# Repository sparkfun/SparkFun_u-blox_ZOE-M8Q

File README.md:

SparkFun u-blox ZOE-M8Q
========================================

[*SparkFun u-blox ZOE-M8Q (GPS-15193)*](https://www.sparkfun.com/products/15193)

The ZOE-M8Q is a high quality GPS with equally impressive configurability.  We broke out the basic pins and added all the supporting circuitry to make this module even easier to use.  

Repository Contents
-------------------

* **/Documentation** - Data sheets, additional product information
* **/Hardware** - Eagle design files (.brd, .sch)
* **/Production** - Production panel files (.brd)

Documentation
--------------
* **[Installing an Arduino Library Guide](https://learn.sparkfun.com/tutorials/installing-an-arduino-library)** - Basic information on how to install an Arduino library.
* **[Library](https://github.com/sparkfun/SparkFun_u-blox_GNSS_Arduino_Library)** - Arduino Library used with the SparkFun ZOE-M8Q 
* **[Hookup Guide](https://learn.sparkfun.com/tutorials/sparkfun-gps-breakout-zoe-m8q-and-sam-m8q-hookup-guide)** - Basic hookup guide for the SparkFun ZOE-M8Q.

License Information
-------------------

This product is _**open source**_! 

Please review the LICENSE.md file for license information. 

If you have any questions or concerns on licensing, please contact technical support on our [SparkFun forums](https://forum.sparkfun.com/viewforum.php?f=152).

Distributed as-is; no warranty is given.

- Your friends at SparkFun.

_<COLLABORATION CREDIT>_

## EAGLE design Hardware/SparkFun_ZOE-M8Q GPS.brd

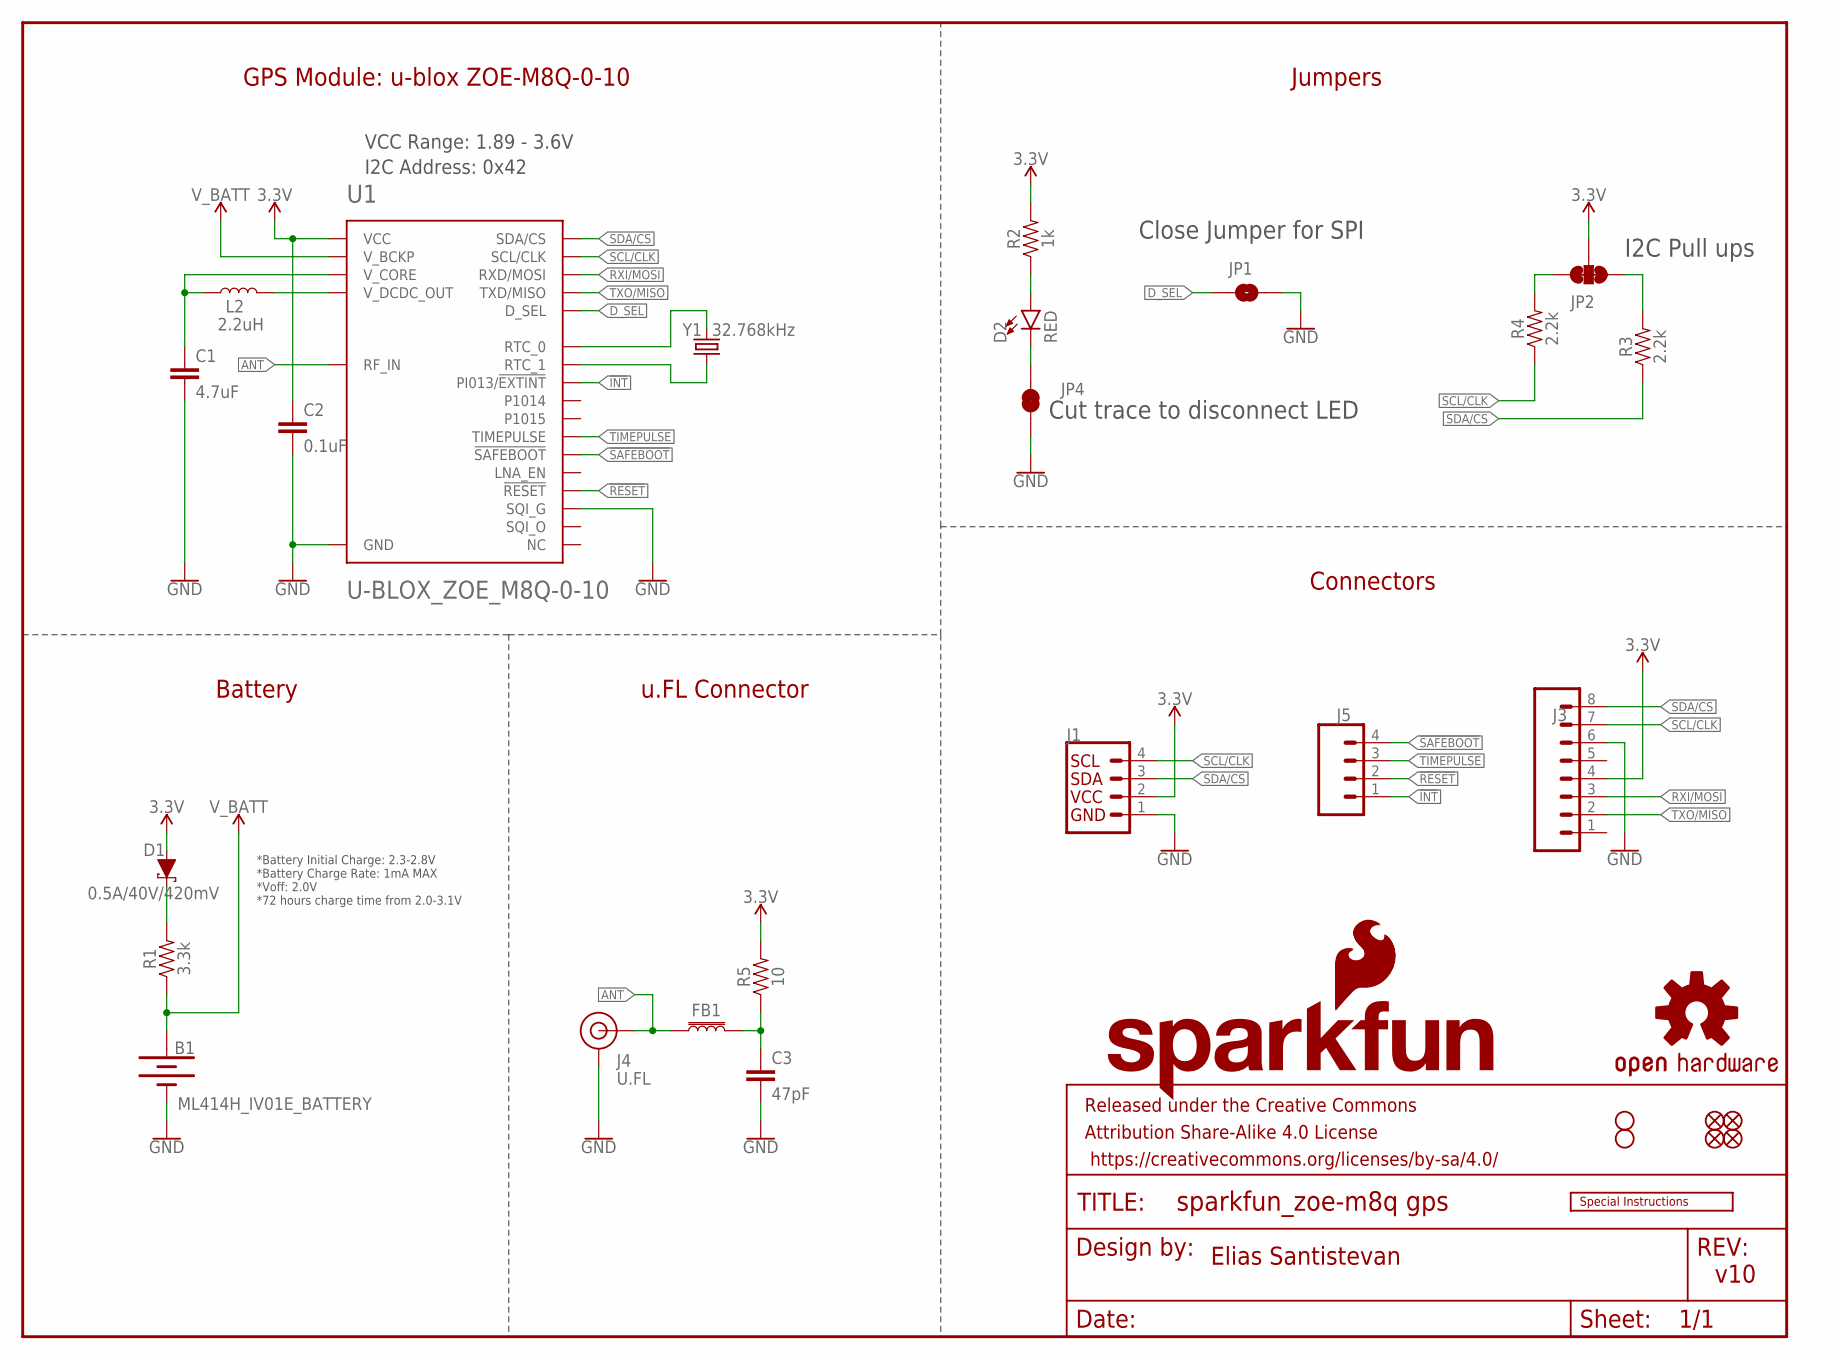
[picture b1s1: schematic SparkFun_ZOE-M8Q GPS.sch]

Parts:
B1: ML414H_IV01E_BATTERY; ML414H_IV01E
C1: 4.7uF; 0603
C2: 0.1uF; 0603
C3: 47pF; 0603
D1: 0.5A/40V/420mV; SOD-323
D2: RED; LED-0603
FB1: FERRITE_BEAD-120_OHM-0402; 0402
FD1, FD2, FD3, FD4: FIDUCIALUFIDUCIAL; FIDUCIAL-MICRO
FRAME1: FRAME-LETTER; CREATIVE_COMMONS
H2, H3: STAND-OFFTIGHT; STAND-OFF-TIGHT
J1: QWIIC_CONNECTORJS-1MM; JST04_1MM_RA
J3: CONN_08NO_SILK_FEMALE_PTH; 1X08_NO_SILK
J4: U.FL
J5: CONN_041X04_NO_SILK; 1X04_NO_SILK
JP1: JUMPER-SMT_2_NO_SILK; SMT-JUMPER_2_NO_SILK
JP2: JUMPER-SMT_3_2-NC_TRACE_SILK; SMT-JUMPER_3_2-NC_TRACE_SILK
JP4: JUMPER-SMT_2_NC_TRACE_SILK; SMT-JUMPER_2_NC_TRACE_SILK
L2: 2.2uH; 0806
LOGO1: SFE_LOGO_NAME_FLAME.1_INCH; SFE_LOGO_NAME_FLAME_.1
LOGO2: OSHW-LOGOS; OSHW-LOGO-S
LOGO3: SFE_LOGO_FLAME.1_INCH; SFE_LOGO_FLAME_.1
LOGO4: SPECIAL_INSTRUCTIONS-ORDERING; ORDERING_INSTRUCTIONS
R1: 3.3k; 0603
R2: 1k; 0603
R3, R4: 2.2k; 0603
R5: 10; 0603
U1: U-BLOX_ZOE_M8Q-0-10; UBLOX_ZOE_M8-0-10
Y1: 32.768kHz; CRYSTAL-SMD-3.2X1.5MM

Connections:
3.3V: C2.1, D1.A, J1.2, J3.4, JP2.2, R2.2, R5.2, U1.24 (VCC), U1.25 (VCC)
!INT: J5.1, U1.43 (PI013/!EXTINT)
!RESET: J5.2, U1.20 (!RESET)
!SAFEBOOT: J5.4, U1.34 (!SAFEBOOT)
ANT: FB1.1, J4.FEED (SIGNAL), U1.4 (RF_IN)
D_SEL: JP1.1, U1.48 (D_SEL)
GND: B1.-, C1.2, C2.2, C3.2, J1.1, J3.6, J4.1 (GND), J4.2 (GND), JP1.2, JP4.1, U1.1 (GND), U1.3 (GND), U1.5 (GND), U1.7 (GND), U1.8 (GND), U1.9 (GND), U1.10 (GND), U1.11 (GND), U1.12 (GND), U1.17 (GND), U1.23 (GND), U1.29 (SQI_G), U1.31 (SQI_G), U1.37 (GND), U1.38 (GND), U1.39 (GND), U1.40 (GND), U1.41 (GND), U1.44 (GND), U1.46 (SQI_G), U1.47 (SQI_G), U1.49 (GND)
unnamed: JP2.1, R3.2
unnamed: D1.C, R1.2
unnamed: JP2.3, R4.2
unnamed: D2.A, R2.1
unnamed: C1.1, L2.1, U1.27 (V_CORE)
unnamed: L2.2, U1.26 (V_DCDC_OUT)
unnamed: D2.C, JP4.2
unnamed: C3.1, FB1.2, R5.1
unnamed: U1.18 (RTC_0), Y1.P$2 (2)
unnamed: U1.19 (RTC_1), Y1.P$1 (1)
RXI/MOSI: J3.3, U1.22 (RXD/MOSI)
SCL/CLK: J1.4, J3.7, R4.1, U1.32 (SCL/CLK)
SDA/CS: J1.3, J3.8, R3.1, U1.2 (SDA/CS)
TIMEPULSE: J5.3, U1.33 (TIMEPULSE)
TXO/MISO: J3.2, U1.21 (TXD/MISO)
V_BATT: B1.+, R1.1, U1.16 (V_BCKP)

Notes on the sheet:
v10
Elias Santistevan
GPS Module: u-blox ZOE-M8Q-0-10
Battery
Connectors
Jumpers
Close Jumper for SPI
I2C Pull ups
Cut trace to disconnect LED
u.FL Connector
*Battery Initial Charge: 2.3-2.8V *Battery Charge Rate: 1mA MAX *Voff: 2.0V *72 hours charge time from 2.0-3.1V
VCC Range: 1.89 - 3.6V
I2C Address: 0x42

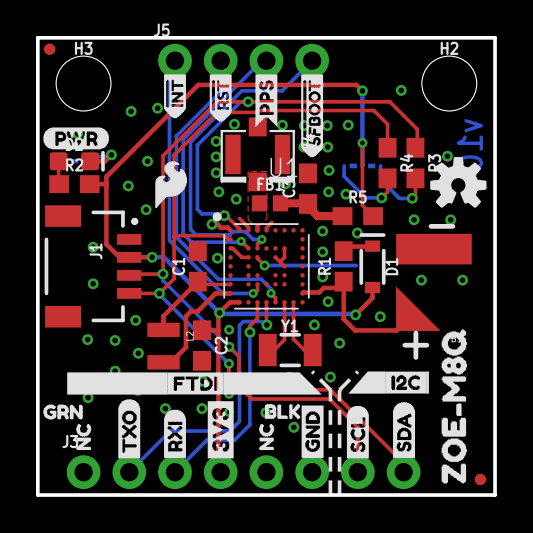
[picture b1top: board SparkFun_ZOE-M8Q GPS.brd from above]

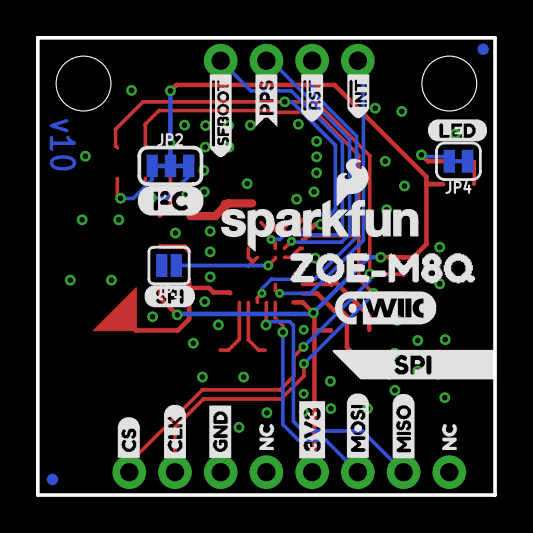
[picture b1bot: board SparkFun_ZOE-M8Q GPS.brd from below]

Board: 2 copper layers, 25.4 x 25.4 mm, 69 parts (24 on the bottom side), 23 nets.

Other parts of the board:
U$1, U$10: 3V3-03
U$2: SDA0
U$3: SCL0
U$4, U$7: GND0
U$5: CS0
U$6: MISO0
U$8: CLK0
U$9, U$17: SPI0
U$11, U$18: #INT0
U$12, U$21: #RST0
U$13, U$23: PPS0
U$14, U$24: #SFBOOT0
U$15: TXO0
U$16, U$30: ZOE#M8Q0
U$19: RXI0
U$20: BLK0
U$22, U$33, U$34, U$35: NC0
U$25: LED0
U$26: PWR-()-03
U$27: MOSI0
U$28: FTDI0
U$29: I2C0
U$31: GRN0
U$32: I_SUPER2_C-()-04
U$36: QWIIC_COPYRIGHT_SMALL

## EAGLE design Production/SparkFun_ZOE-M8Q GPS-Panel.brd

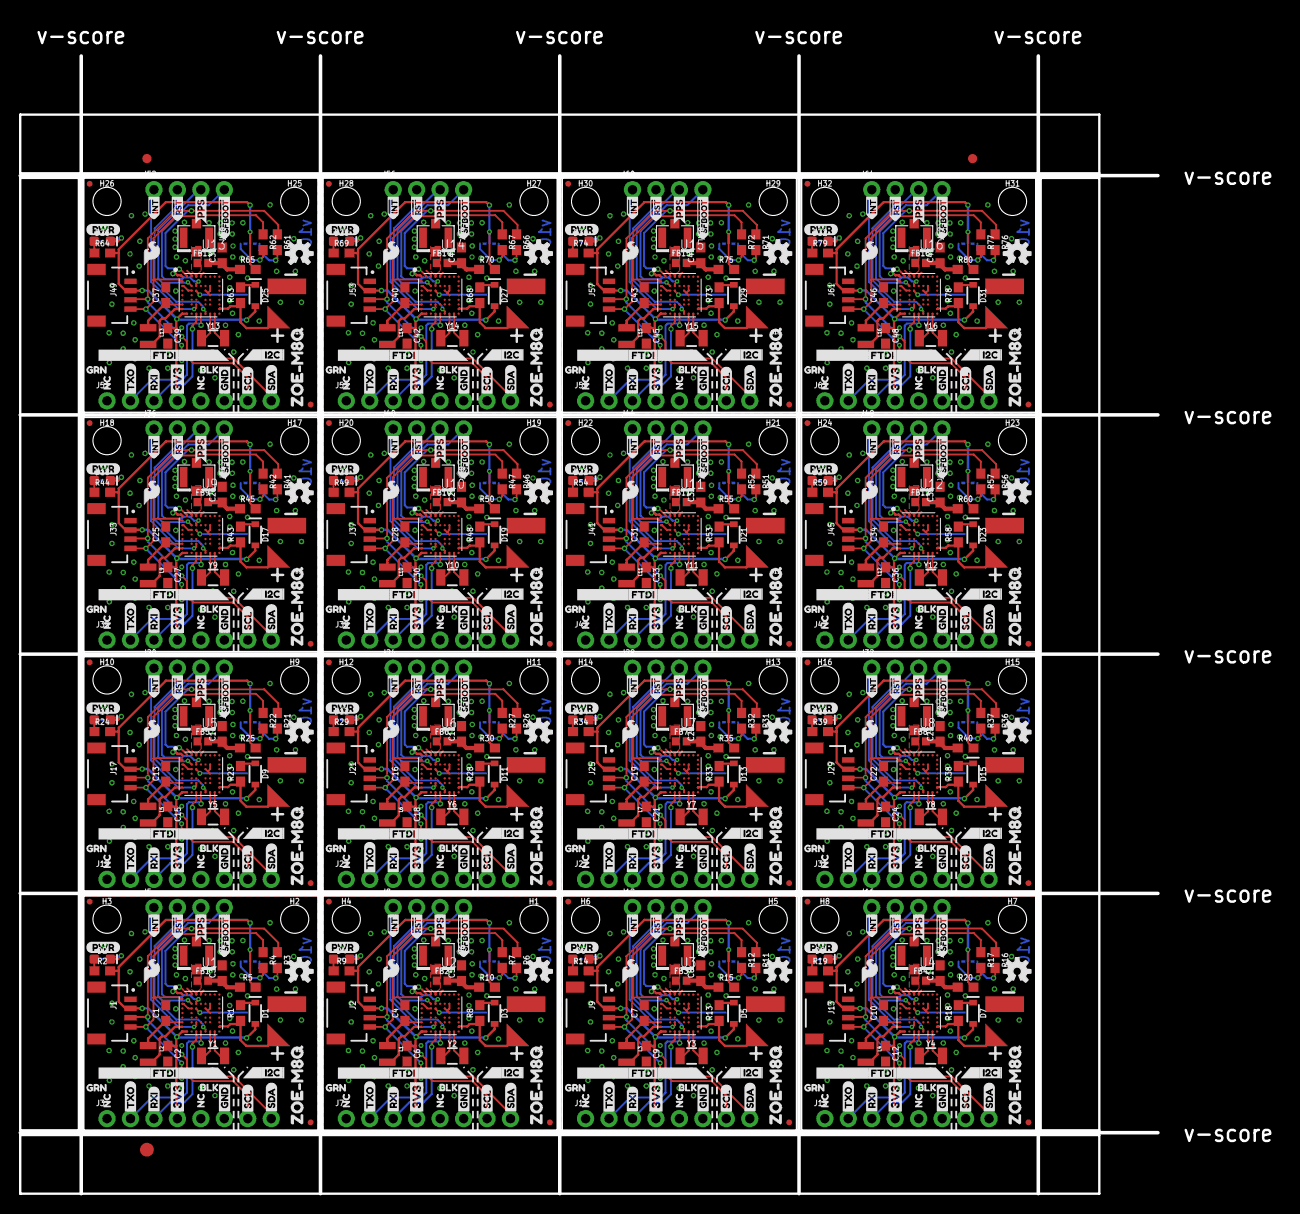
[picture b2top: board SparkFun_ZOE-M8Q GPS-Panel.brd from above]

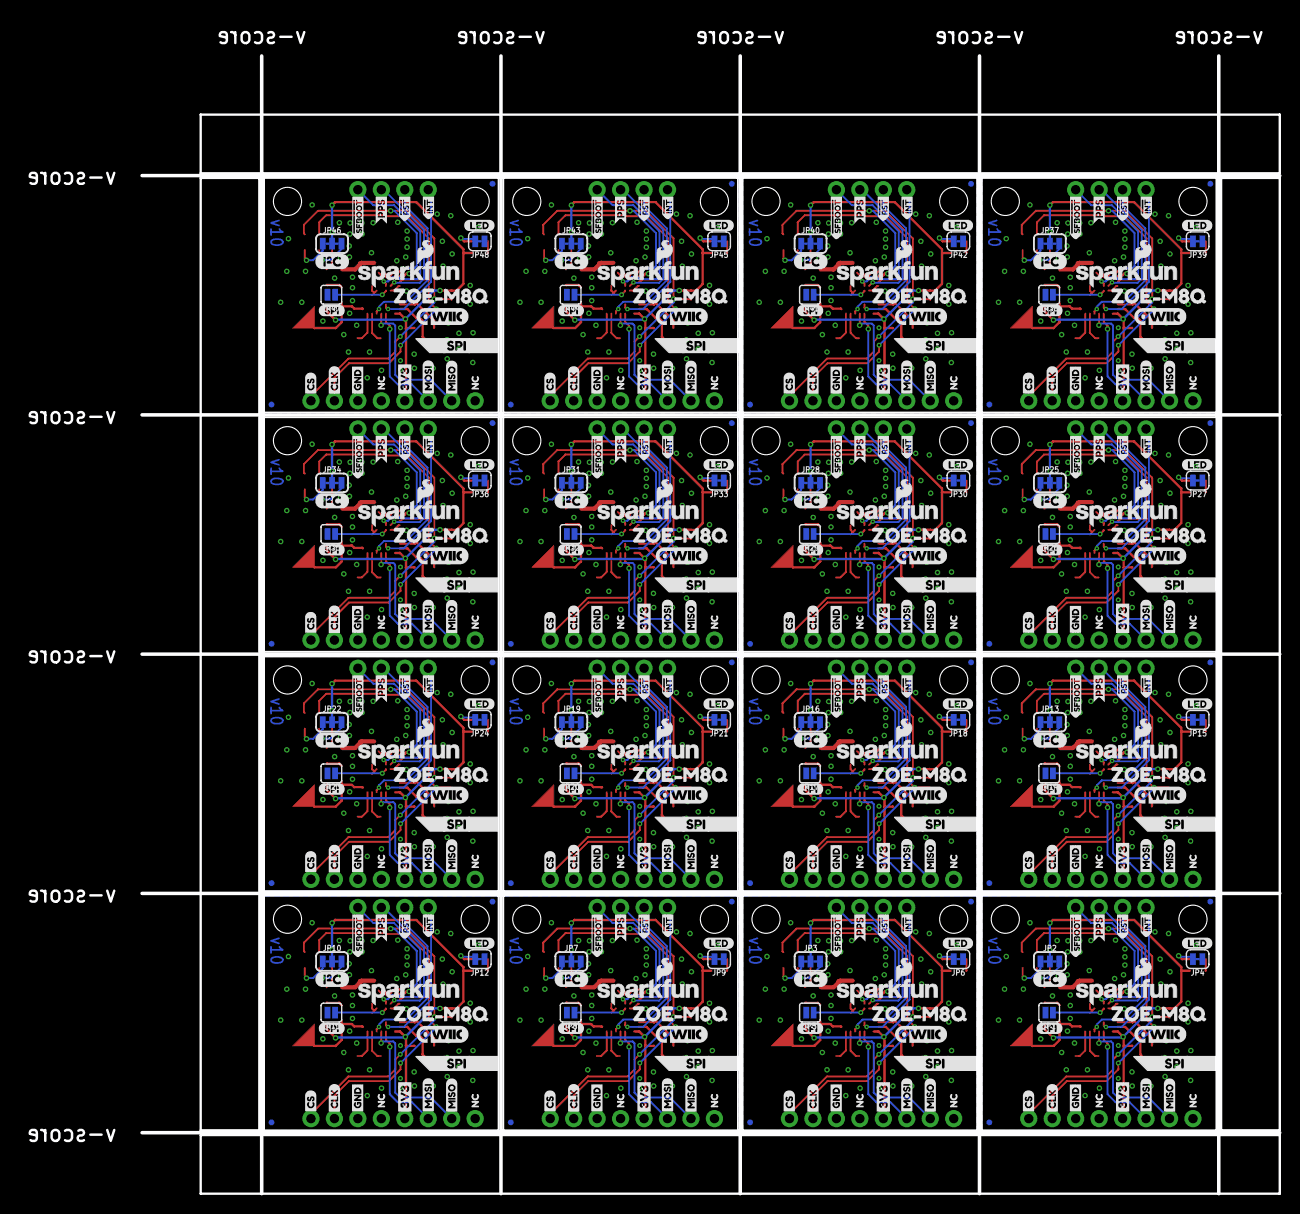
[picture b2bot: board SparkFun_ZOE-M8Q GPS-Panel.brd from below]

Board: 2 copper layers, 136.4 x 127.1 mm, 1075 parts (384 on the bottom side), 368 nets.

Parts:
B1, B2, B3, B4, B5, B6, B7, B8, B9, B10, B11, B12, B13, B14, B15, B16: ML414H_IV01E_BATTERY; ML414H_IV01E
C1, C4, C7, C10, C13, C16, C19, C22, C25, C28, C31, C34, C37, C40, C43, C46: 4.7uF; 0603
C2, C6, C9, C12, C15, C18, C21, C24, C27, C30, C33, C36, C39, C42, C45, C48: 0.1uF; 0603
C3, C5, C8, C11, C14, C17, C20, C23, C26, C29, C32, C35, C38, C41, C44, C47: 47pF; 0603
D1, D3, D5, D7, D9, D11, D13, D15, D17, D19, D21, D23, D25, D27, D29, D31: 0.5A/40V/420mV; SOD-323
D2, D4, D6, D8, D10, D12, D14, D16, D18, D20, D22, D24, D26, D28, D30, D32: RED; LED-0603
E$1, E$2: FIDUCIAL-1X2
E$3: FIDUCIAL-1.5X3
FB1, FB2, FB3, FB4, FB5, FB6, FB7, FB8, FB9, FB10, FB11, FB12, FB13, FB14, FB15, FB16: FERRITE_BEAD-120_OHM-0402; 0402
FD1, FD2, FD3, FD4, FD5, FD6, FD7, FD8, FD9, FD10, FD11, FD12, FD13, FD14, FD15, FD16, FD17, FD18, FD19, FD20, FD21, FD22, FD23, FD24, FD25, FD26, FD27, FD28, FD29, FD30, FD31, FD32, FD33, FD34, FD35, FD36, FD37, FD38, FD39, FD40, FD41, FD42, FD43, FD44, FD45, FD46, FD47, FD48, FD49, FD50, FD51, FD52, FD53, FD54, FD55, FD56, FD57, FD58, FD59, FD60, FD61, FD62, FD63, FD64: FIDUCIALUFIDUCIAL; FIDUCIAL-MICRO
H1, H2, H3, H4, H5, H6, H7, H8, H9, H10, H11, H12, H13, H14, H15, H16, H17, H18, H19, H20, H21, H22, H23, H24, H25, H26, H27, H28, H29, H30, H31, H32: STAND-OFFTIGHT; STAND-OFF-TIGHT
J1, J2, J9, J13, J17, J21, J25, J29, J33, J37, J41, J45, J49, J53, J57, J61: JST04_1MM_RA
J3, J7, J11, J15, J19, J23, J27, J31, J35, J39, J43, J47, J51, J55, J59, J63: 1X08_NO_SILK
J4, J6, J10, J14, J18, J22, J26, J30, J34, J38, J42, J46, J50, J54, J58, J62: U.FL
J5, J8, J12, J16, J20, J24, J28, J32, J36, J40, J44, J48, J52, J56, J60, J64: 1X04_NO_SILK
JP1, JP5, JP8, JP11, JP14, JP17, JP20, JP23, JP26, JP29, JP32, JP35, JP38, JP41, JP44, JP47: JUMPER-SMT_2_NO_SILK; SMT-JUMPER_2_NO_SILK
JP2, JP3, JP7, JP10, JP13, JP16, JP19, JP22, JP25, JP28, JP31, JP34, JP37, JP40, JP43, JP46: JUMPER-SMT_3_2-NC_TRACE_SILK; SMT-JUMPER_3_2-NC_TRACE_SILK
JP4, JP6, JP9, JP12, JP15, JP18, JP21, JP24, JP27, JP30, JP33, JP36, JP39, JP42, JP45, JP48: JUMPER-SMT_2_NC_TRACE_SILK; SMT-JUMPER_2_NC_TRACE_SILK
L1, L2, L3, L4, L5, L6, L7, L8, L9, L10, L11, L12, L13, L14, L15, L16: 2.2uH; 0806
LOGO1, LOGO4, LOGO7, LOGO10, LOGO13, LOGO16, LOGO19, LOGO22, LOGO25, LOGO28, LOGO31, LOGO34, LOGO37, LOGO40, LOGO43, LOGO46: SFE_LOGO_NAME_FLAME.1_INCH; SFE_LOGO_NAME_FLAME_.1
LOGO2, LOGO5, LOGO8, LOGO11, LOGO14, LOGO17, LOGO20, LOGO23, LOGO26, LOGO29, LOGO32, LOGO35, LOGO38, LOGO41, LOGO44, LOGO47: OSHW-LOGOS; OSHW-LOGO-S
LOGO3, LOGO6, LOGO9, LOGO12, LOGO15, LOGO18, LOGO21, LOGO24, LOGO27, LOGO30, LOGO33, LOGO36, LOGO39, LOGO42, LOGO45, LOGO48: SFE_LOGO_FLAME.1_INCH; SFE_LOGO_FLAME_.1
R1, R8, R13, R18, R23, R28, R33, R38, R43, R48, R53, R58, R63, R68, R73, R78: 3.3k; 0603
R2, R9, R14, R19, R24, R29, R34, R39, R44, R49, R54, R59, R64, R69, R74, R79: 1k; 0603
R3, R4, R6, R7, R11, R12, R16, R17, R21, R22, R26, R27, R31, R32, R36, R37, R41, R42, R46, R47, R51, R52, R56, R57, R61, R62, R66, R67, R71, R72, R76, R77: 2.2k; 0603
R5, R10, R15, R20, R25, R30, R35, R40, R45, R50, R55, R60, R65, R70, R75, R80: 10; 0603
U1, U2, U3, U4, U5, U6, U7, U8, U9, U10, U11, U12, U13, U14, U15, U16: UBLOX_ZOE_M8-0-10
U$1, U$10, U$37, U$43, U$73, U$79, U$109, U$115, U$145, U$151, U$181, U$187, U$217, U$223, U$253, U$259, U$289, U$295, U$325, U$331, U$361, U$367, U$397, U$403, U$433, U$439, U$469, U$475, U$505, U$511, U$541, U$547: 3V3-03
U$2, U$38, U$74, U$110, U$146, U$182, U$218, U$254, U$290, U$326, U$362, U$398, U$434, U$470, U$506, U$542: SDA0
U$3, U$39, U$75, U$111, U$147, U$183, U$219, U$255, U$291, U$327, U$363, U$399, U$435, U$471, U$507, U$543: SCL0
U$4, U$7, U$40, U$41, U$76, U$77, U$112, U$113, U$148, U$149, U$184, U$185, U$220, U$221, U$256, U$257, U$292, U$293, U$328, U$329, U$364, U$365, U$400, U$401, U$436, U$437, U$472, U$473, U$508, U$509, U$544, U$545: GND0
U$5, U$56, U$92, U$128, U$164, U$200, U$236, U$272, U$308, U$344, U$380, U$416, U$452, U$488, U$524, U$560: CS0
U$6, U$54, U$90, U$126, U$162, U$198, U$234, U$270, U$306, U$342, U$378, U$414, U$450, U$486, U$522, U$558: MISO0
U$8, U$42, U$78, U$114, U$150, U$186, U$222, U$258, U$294, U$330, U$366, U$402, U$438, U$474, U$510, U$546: CLK0
U$9, U$17, U$45, U$57, U$81, U$93, U$117, U$129, U$153, U$165, U$189, U$201, U$225, U$237, U$261, U$273, U$297, U$309, U$333, U$345, U$369, U$381, U$405, U$417, U$441, U$453, U$477, U$489, U$513, U$525, U$549, U$561: SPI0
U$11, U$18, U$64, U$65, U$100, U$101, U$136, U$137, U$172, U$173, U$208, U$209, U$244, U$245, U$280, U$281, U$316, U$317, U$352, U$353, U$388, U$389, U$424, U$425, U$460, U$461, U$496, U$497, U$532, U$533, U$568, U$569: #INT0
U$12, U$21, U$66, U$67, U$102, U$103, U$138, U$139, U$174, U$175, U$210, U$211, U$246, U$247, U$282, U$283, U$318, U$319, U$354, U$355, U$390, U$391, U$426, U$427, U$462, U$463, U$498, U$499, U$534, U$535, U$570, U$571: #RST0
U$13, U$23, U$46, U$47, U$82, U$83, U$118, U$119, U$154, U$155, U$190, U$191, U$226, U$227, U$262, U$263, U$298, U$299, U$334, U$335, U$370, U$371, U$406, U$407, U$442, U$443, U$478, U$479, U$514, U$515, U$550, U$551: PPS0
U$14, U$24, U$48, U$49, U$84, U$85, U$120, U$121, U$156, U$157, U$192, U$193, U$228, U$229, U$264, U$265, U$300, U$301, U$336, U$337, U$372, U$373, U$408, U$409, U$444, U$445, U$480, U$481, U$516, U$517, U$552, U$553: #SFBOOT0
U$15, U$52, U$88, U$124, U$160, U$196, U$232, U$268, U$304, U$340, U$376, U$412, U$448, U$484, U$520, U$556: TXO0
U$16, U$30, U$44, U$60, U$80, U$96, U$116, U$132, U$152, U$168, U$188, U$204, U$224, U$240, U$260, U$276, U$296, U$312, U$332, U$348, U$368, U$384, U$404, U$420, U$440, U$456, U$476, U$492, U$512, U$528, U$548, U$564: ZOE#M8Q0
U$19, U$53, U$89, U$125, U$161, U$197, U$233, U$269, U$305, U$341, U$377, U$413, U$449, U$485, U$521, U$557: RXI0
U$20, U$61, U$97, U$133, U$169, U$205, U$241, U$277, U$313, U$349, U$385, U$421, U$457, U$493, U$529, U$565: BLK0
U$22, U$33, U$34, U$35, U$68, U$69, U$70, U$71, U$104, U$105, U$106, U$107, U$140, U$141, U$142, U$143, U$176, U$177, U$178, U$179, U$212, U$213, U$214, U$215, U$248, U$249, U$250, U$251, U$284, U$285, U$286, U$287, U$320, U$321, U$322, U$323, U$356, U$357, U$358, U$359, U$392, U$393, U$394, U$395, U$428, U$429, U$430, U$431, U$464, U$465, U$466, U$467, U$500, U$501, U$502, U$503, U$536, U$537, U$538, U$539, U$572, U$573, U$574, U$575: NC0
U$25, U$50, U$86, U$122, U$158, U$194, U$230, U$266, U$302, U$338, U$374, U$410, U$446, U$482, U$518, U$554: LED0
U$26, U$51, U$87, U$123, U$159, U$195, U$231, U$267, U$303, U$339, U$375, U$411, U$447, U$483, U$519, U$555: PWR-()-03
U$27, U$55, U$91, U$127, U$163, U$199, U$235, U$271, U$307, U$343, U$379, U$415, U$451, U$487, U$523, U$559: MOSI0
U$28, U$58, U$94, U$130, U$166, U$202, U$238, U$274, U$310, U$346, U$382, U$418, U$454, U$490, U$526, U$562: FTDI0
U$29, U$59, U$95, U$131, U$167, U$203, U$239, U$275, U$311, U$347, U$383, U$419, U$455, U$491, U$527, U$563: I2C0
U$31, U$62, U$98, U$134, U$170, U$206, U$242, U$278, U$314, U$350, U$386, U$422, U$458, U$494, U$530, U$566: GRN0
U$32, U$63, U$99, U$135, U$171, U$207, U$243, U$279, U$315, U$351, U$387, U$423, U$459, U$495, U$531, U$567: I_SUPER2_C-()-04
U$36, U$72, U$108, U$144, U$180, U$216, U$252, U$288, U$324, U$360, U$396, U$432, U$468, U$504, U$540, U$576: QWIIC_COPYRIGHT_SMALL
Y1, Y2, Y3, Y4, Y5, Y6, Y7, Y8, Y9, Y10, Y11, Y12, Y13, Y14, Y15, Y16: 32.768kHz; CRYSTAL-SMD-3.2X1.5MM

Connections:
3.3V: C2.1, D1.A, J1.2, J3.4, JP2.2, R2.2, R5.2, U1.24, U1.25
3.3V1: C6.1, D3.A, J2.2, J7.4, JP3.2, R9.2, R10.2, U2.24, U2.25
3.3V2: C9.1, D5.A, J9.2, J11.4, JP7.2, R14.2, R15.2, U3.24, U3.25
3.3V3: C12.1, D7.A, J13.2, J15.4, JP10.2, R19.2, R20.2, U4.24, U4.25
3.3V4: C15.1, D9.A, J17.2, J19.4, JP13.2, R24.2, R25.2, U5.24, U5.25
3.3V5: C18.1, D11.A, J21.2, J23.4, JP16.2, R29.2, R30.2, U6.24, U6.25
3.3V6: C21.1, D13.A, J25.2, J27.4, JP19.2, R34.2, R35.2, U7.24, U7.25
3.3V7: C24.1, D15.A, J29.2, J31.4, JP22.2, R39.2, R40.2, U8.24, U8.25
3.3V8: C27.1, D17.A, J33.2, J35.4, JP25.2, R44.2, R45.2, U9.24, U9.25
3.3V9: C30.1, D19.A, J37.2, J39.4, JP28.2, R49.2, R50.2, U10.24, U10.25
3.3V10: C33.1, D21.A, J41.2, J43.4, JP31.2, R54.2, R55.2, U11.24, U11.25
3.3V11: C36.1, D23.A, J45.2, J47.4, JP34.2, R59.2, R60.2, U12.24, U12.25
3.3V12: C39.1, D25.A, J49.2, J51.4, JP37.2, R64.2, R65.2, U13.24, U13.25
3.3V13: C42.1, D27.A, J53.2, J55.4, JP40.2, R69.2, R70.2, U14.24, U14.25
3.3V14: C45.1, D29.A, J57.2, J59.4, JP43.2, R74.2, R75.2, U15.24, U15.25
3.3V15: C48.1, D31.A, J61.2, J63.4, JP46.2, R79.2, R80.2, U16.24, U16.25
!INT: J5.1, U1.43
!INT1: J8.1, U2.43
!INT2: J12.1, U3.43
!INT3: J16.1, U4.43
!INT4: J20.1, U5.43
!INT5: J24.1, U6.43
!INT6: J28.1, U7.43
!INT7: J32.1, U8.43
!INT8: J36.1, U9.43
!INT9: J40.1, U10.43
!INT10: J44.1, U11.43
!INT11: J48.1, U12.43
!INT12: J52.1, U13.43
!INT13: J56.1, U14.43
!INT14: J60.1, U15.43
!INT15: J64.1, U16.43
!RESET: J5.2, U1.20
!RESET1: J8.2, U2.20
!RESET2: J12.2, U3.20
!RESET3: J16.2, U4.20
!RESET4: J20.2, U5.20
!RESET5: J24.2, U6.20
!RESET6: J28.2, U7.20
!RESET7: J32.2, U8.20
!RESET8: J36.2, U9.20
!RESET9: J40.2, U10.20
!RESET10: J44.2, U11.20
!RESET11: J48.2, U12.20
!RESET12: J52.2, U13.20
!RESET13: J56.2, U14.20
!RESET14: J60.2, U15.20
!RESET15: J64.2, U16.20
!SAFEBOOT: J5.4, U1.34
!SAFEBOOT1: J8.4, U2.34
!SAFEBOOT2: J12.4, U3.34
!SAFEBOOT3: J16.4, U4.34
!SAFEBOOT4: J20.4, U5.34
!SAFEBOOT5: J24.4, U6.34
!SAFEBOOT6: J28.4, U7.34
!SAFEBOOT7: J32.4, U8.34
!SAFEBOOT8: J36.4, U9.34
!SAFEBOOT9: J40.4, U10.34
!SAFEBOOT10: J44.4, U11.34
!SAFEBOOT11: J48.4, U12.34
!SAFEBOOT12: J52.4, U13.34
!SAFEBOOT13: J56.4, U14.34
!SAFEBOOT14: J60.4, U15.34
!SAFEBOOT15: J64.4, U16.34
ANT: FB1.1, J4.FEED, U1.4
ANT1: FB2.1, J6.FEED, U2.4
ANT2: FB3.1, J10.FEED, U3.4
ANT3: FB4.1, J14.FEED, U4.4
ANT4: FB5.1, J18.FEED, U5.4
ANT5: FB6.1, J22.FEED, U6.4
ANT6: FB7.1, J26.FEED, U7.4
ANT7: FB8.1, J30.FEED, U8.4
ANT8: FB9.1, J34.FEED, U9.4
ANT9: FB10.1, J38.FEED, U10.4
ANT10: FB11.1, J42.FEED, U11.4
ANT11: FB12.1, J46.FEED, U12.4
ANT12: FB13.1, J50.FEED, U13.4
ANT13: FB14.1, J54.FEED, U14.4
ANT14: FB15.1, J58.FEED, U15.4
ANT15: FB16.1, J62.FEED, U16.4
D_SEL: JP1.1, U1.48
D_SEL1: JP5.1, U2.48
D_SEL2: JP8.1, U3.48
D_SEL3: JP11.1, U4.48
D_SEL4: JP14.1, U5.48
D_SEL5: JP17.1, U6.48
D_SEL6: JP20.1, U7.48
D_SEL7: JP23.1, U8.48
D_SEL8: JP26.1, U9.48
D_SEL9: JP29.1, U10.48
D_SEL10: JP32.1, U11.48
D_SEL11: JP35.1, U12.48
D_SEL12: JP38.1, U13.48
D_SEL13: JP41.1, U14.48
D_SEL14: JP44.1, U15.48
D_SEL15: JP47.1, U16.48
GND: B1.-, C1.2, C2.2, C3.2, J1.1, J3.6, J4.1, J4.2, JP1.2, JP4.1, U1.1, U1.3, U1.5, U1.7, U1.8, U1.9, U1.10, U1.11, U1.12, U1.17, U1.23, U1.29, U1.31, U1.37, U1.38, U1.39, U1.40, U1.41, U1.44, U1.46, U1.47, U1.49
GND1: B2.-, C4.2, C5.2, C6.2, J2.1, J6.1, J6.2, J7.6, JP5.2, JP6.1, U2.1, U2.3, U2.5, U2.7, U2.8, U2.9, U2.10, U2.11, U2.12, U2.17, U2.23, U2.29, U2.31, U2.37, U2.38, U2.39, U2.40, U2.41, U2.44, U2.46, U2.47, U2.49
GND2: B3.-, C7.2, C8.2, C9.2, J9.1, J10.1, J10.2, J11.6, JP8.2, JP9.1, U3.1, U3.3, U3.5, U3.7, U3.8, U3.9, U3.10, U3.11, U3.12, U3.17, U3.23, U3.29, U3.31, U3.37, U3.38, U3.39, U3.40, U3.41, U3.44, U3.46, U3.47, U3.49
GND3: B4.-, C10.2, C11.2, C12.2, J13.1, J14.1, J14.2, J15.6, JP11.2, JP12.1, U4.1, U4.3, U4.5, U4.7, U4.8, U4.9, U4.10, U4.11, U4.12, U4.17, U4.23, U4.29, U4.31, U4.37, U4.38, U4.39, U4.40, U4.41, U4.44, U4.46, U4.47, U4.49
GND4: B5.-, C13.2, C14.2, C15.2, J17.1, J18.1, J18.2, J19.6, JP14.2, JP15.1, U5.1, U5.3, U5.5, U5.7, U5.8, U5.9, U5.10, U5.11, U5.12, U5.17, U5.23, U5.29, U5.31, U5.37, U5.38, U5.39, U5.40, U5.41, U5.44, U5.46, U5.47, U5.49
GND5: B6.-, C16.2, C17.2, C18.2, J21.1, J22.1, J22.2, J23.6, JP17.2, JP18.1, U6.1, U6.3, U6.5, U6.7, U6.8, U6.9, U6.10, U6.11, U6.12, U6.17, U6.23, U6.29, U6.31, U6.37, U6.38, U6.39, U6.40, U6.41, U6.44, U6.46, U6.47, U6.49
GND6: B7.-, C19.2, C20.2, C21.2, J25.1, J26.1, J26.2, J27.6, JP20.2, JP21.1, U7.1, U7.3, U7.5, U7.7, U7.8, U7.9, U7.10, U7.11, U7.12, U7.17, U7.23, U7.29, U7.31, U7.37, U7.38, U7.39, U7.40, U7.41, U7.44, U7.46, U7.47, U7.49
GND7: B8.-, C22.2, C23.2, C24.2, J29.1, J30.1, J30.2, J31.6, JP23.2, JP24.1, U8.1, U8.3, U8.5, U8.7, U8.8, U8.9, U8.10, U8.11, U8.12, U8.17, U8.23, U8.29, U8.31, U8.37, U8.38, U8.39, U8.40, U8.41, U8.44, U8.46, U8.47, U8.49
GND8: B9.-, C25.2, C26.2, C27.2, J33.1, J34.1, J34.2, J35.6, JP26.2, JP27.1, U9.1, U9.3, U9.5, U9.7, U9.8, U9.9, U9.10, U9.11, U9.12, U9.17, U9.23, U9.29, U9.31, U9.37, U9.38, U9.39, U9.40, U9.41, U9.44, U9.46, U9.47, U9.49
GND9: B10.-, C28.2, C29.2, C30.2, J37.1, J38.1, J38.2, J39.6, JP29.2, JP30.1, U10.1, U10.3, U10.5, U10.7, U10.8, U10.9, U10.10, U10.11, U10.12, U10.17, U10.23, U10.29, U10.31, U10.37, U10.38, U10.39, U10.40, U10.41, U10.44, U10.46, U10.47, U10.49
GND10: B11.-, C31.2, C32.2, C33.2, J41.1, J42.1, J42.2, J43.6, JP32.2, JP33.1, U11.1, U11.3, U11.5, U11.7, U11.8, U11.9, U11.10, U11.11, U11.12, U11.17, U11.23, U11.29, U11.31, U11.37, U11.38, U11.39, U11.40, U11.41, U11.44, U11.46, U11.47, U11.49
GND11: B12.-, C34.2, C35.2, C36.2, J45.1, J46.1, J46.2, J47.6, JP35.2, JP36.1, U12.1, U12.3, U12.5, U12.7, U12.8, U12.9, U12.10, U12.11, U12.12, U12.17, U12.23, U12.29, U12.31, U12.37, U12.38, U12.39, U12.40, U12.41, U12.44, U12.46, U12.47, U12.49
GND12: B13.-, C37.2, C38.2, C39.2, J49.1, J50.1, J50.2, J51.6, JP38.2, JP39.1, U13.1, U13.3, U13.5, U13.7, U13.8, U13.9, U13.10, U13.11, U13.12, U13.17, U13.23, U13.29, U13.31, U13.37, U13.38, U13.39, U13.40, U13.41, U13.44, U13.46, U13.47, U13.49
GND13: B14.-, C40.2, C41.2, C42.2, J53.1, J54.1, J54.2, J55.6, JP41.2, JP42.1, U14.1, U14.3, U14.5, U14.7, U14.8, U14.9, U14.10, U14.11, U14.12, U14.17, U14.23, U14.29, U14.31, U14.37, U14.38, U14.39, U14.40, U14.41, U14.44, U14.46, U14.47, U14.49
GND14: B15.-, C43.2, C44.2, C45.2, J57.1, J58.1, J58.2, J59.6, JP44.2, JP45.1, U15.1, U15.3, U15.5, U15.7, U15.8, U15.9, U15.10, U15.11, U15.12, U15.17, U15.23, U15.29, U15.31, U15.37, U15.38, U15.39, U15.40, U15.41, U15.44, U15.46, U15.47, U15.49
GND15: B16.-, C46.2, C47.2, C48.2, J61.1, J62.1, J62.2, J63.6, JP47.2, JP48.1, U16.1, U16.3, U16.5, U16.7, U16.8, U16.9, U16.10, U16.11, U16.12, U16.17, U16.23, U16.29, U16.31, U16.37, U16.38, U16.39, U16.40, U16.41, U16.44, U16.46, U16.47, U16.49
unnamed: JP2.1, R3.2
unnamed: D1.C, R1.2
unnamed: JP2.3, R4.2
unnamed: D2.A, R2.1
unnamed: L1.2, U2.26
unnamed: C1.1, L2.1, U1.27
unnamed: L2.2, U1.26
unnamed: D2.C, JP4.2
unnamed: C3.1, FB1.2, R5.1
unnamed: C4.1, L1.1, U2.27
unnamed: U2.18, Y2.P$2
unnamed: U2.19, Y2.P$1
unnamed: U1.18, Y1.P$2
unnamed: D3.C, R8.2
unnamed: U1.19, Y1.P$1
unnamed: JP3.1, R6.2
unnamed: JP3.3, R7.2
unnamed: D4.A, R9.1
unnamed: D4.C, JP6.2
unnamed: C5.1, FB2.2, R10.1
unnamed: L3.2, U3.26
unnamed: C7.1, L3.1, U3.27
unnamed: U3.18, Y3.P$2
unnamed: U3.19, Y3.P$1
unnamed: D5.C, R13.2
unnamed: JP7.1, R11.2
unnamed: JP7.3, R12.2
unnamed: D6.A, R14.1
unnamed: D6.C, JP9.2
unnamed: C8.1, FB3.2, R15.1
unnamed: L4.2, U4.26
unnamed: C10.1, L4.1, U4.27
unnamed: U4.18, Y4.P$2
unnamed: U4.19, Y4.P$1
unnamed: D7.C, R18.2
unnamed: JP10.1, R16.2
unnamed: JP10.3, R17.2
unnamed: D8.A, R19.1
unnamed: D8.C, JP12.2
unnamed: C11.1, FB4.2, R20.1
unnamed: L5.2, U5.26
unnamed: C13.1, L5.1, U5.27
unnamed: U5.18, Y5.P$2
unnamed: U5.19, Y5.P$1
unnamed: D9.C, R23.2
unnamed: JP13.1, R21.2
unnamed: JP13.3, R22.2
unnamed: D10.A, R24.1
unnamed: D10.C, JP15.2
unnamed: C14.1, FB5.2, R25.1
unnamed: L6.2, U6.26
unnamed: C16.1, L6.1, U6.27
unnamed: U6.18, Y6.P$2
unnamed: U6.19, Y6.P$1
unnamed: D11.C, R28.2
unnamed: JP16.1, R26.2
unnamed: JP16.3, R27.2
unnamed: D12.A, R29.1
unnamed: D12.C, JP18.2
unnamed: C17.1, FB6.2, R30.1
unnamed: L7.2, U7.26
unnamed: C19.1, L7.1, U7.27
unnamed: U7.18, Y7.P$2
unnamed: U7.19, Y7.P$1
unnamed: D13.C, R33.2
unnamed: JP19.1, R31.2
unnamed: JP19.3, R32.2
unnamed: D14.A, R34.1
unnamed: D14.C, JP21.2
unnamed: C20.1, FB7.2, R35.1
unnamed: L8.2, U8.26
unnamed: C22.1, L8.1, U8.27
unnamed: U8.18, Y8.P$2
unnamed: U8.19, Y8.P$1
unnamed: D15.C, R38.2
unnamed: JP22.1, R36.2
unnamed: JP22.3, R37.2
unnamed: D16.A, R39.1
unnamed: D16.C, JP24.2
unnamed: C23.1, FB8.2, R40.1
unnamed: L9.2, U9.26
unnamed: C25.1, L9.1, U9.27
unnamed: U9.18, Y9.P$2
unnamed: U9.19, Y9.P$1
unnamed: D17.C, R43.2
unnamed: JP25.1, R41.2
unnamed: JP25.3, R42.2
unnamed: D18.A, R44.1
unnamed: D18.C, JP27.2
unnamed: C26.1, FB9.2, R45.1
unnamed: L10.2, U10.26
unnamed: C28.1, L10.1, U10.27
unnamed: U10.18, Y10.P$2
unnamed: U10.19, Y10.P$1
unnamed: D19.C, R48.2
unnamed: JP28.1, R46.2
unnamed: JP28.3, R47.2
unnamed: D20.A, R49.1
unnamed: D20.C, JP30.2
unnamed: C29.1, FB10.2, R50.1
unnamed: L11.2, U11.26
unnamed: C31.1, L11.1, U11.27
unnamed: U11.18, Y11.P$2
unnamed: U11.19, Y11.P$1
unnamed: D21.C, R53.2
unnamed: JP31.1, R51.2
unnamed: JP31.3, R52.2
unnamed: D22.A, R54.1
unnamed: D22.C, JP33.2
unnamed: C32.1, FB11.2, R55.1
unnamed: L12.2, U12.26
unnamed: C34.1, L12.1, U12.27
unnamed: U12.18, Y12.P$2
unnamed: U12.19, Y12.P$1
unnamed: D23.C, R58.2
unnamed: JP34.1, R56.2
unnamed: JP34.3, R57.2
unnamed: D24.A, R59.1
unnamed: D24.C, JP36.2
unnamed: C35.1, FB12.2, R60.1
unnamed: L13.2, U13.26
unnamed: C37.1, L13.1, U13.27
unnamed: U13.18, Y13.P$2
unnamed: U13.19, Y13.P$1
unnamed: D25.C, R63.2
unnamed: JP37.1, R61.2
unnamed: JP37.3, R62.2
unnamed: D26.A, R64.1
unnamed: D26.C, JP39.2
unnamed: C38.1, FB13.2, R65.1
unnamed: L14.2, U14.26
unnamed: C40.1, L14.1, U14.27
unnamed: U14.18, Y14.P$2
unnamed: U14.19, Y14.P$1
unnamed: D27.C, R68.2
unnamed: JP40.1, R66.2
unnamed: JP40.3, R67.2
unnamed: D28.A, R69.1
unnamed: D28.C, JP42.2
unnamed: C41.1, FB14.2, R70.1
unnamed: L15.2, U15.26
unnamed: C43.1, L15.1, U15.27
unnamed: U15.18, Y15.P$2
unnamed: U15.19, Y15.P$1
unnamed: D29.C, R73.2
unnamed: JP43.1, R71.2
unnamed: JP43.3, R72.2
unnamed: D30.A, R74.1
unnamed: D30.C, JP45.2
unnamed: C44.1, FB15.2, R75.1
unnamed: L16.2, U16.26
unnamed: C46.1, L16.1, U16.27
unnamed: U16.18, Y16.P$2
unnamed: U16.19, Y16.P$1
unnamed: D31.C, R78.2
unnamed: JP46.1, R76.2
unnamed: JP46.3, R77.2
unnamed: D32.A, R79.1
unnamed: D32.C, JP48.2
unnamed: C47.1, FB16.2, R80.1
RXI/MOSI: J3.3, U1.22
RXI/MOSI1: J7.3, U2.22
RXI/MOSI2: J11.3, U3.22
RXI/MOSI3: J15.3, U4.22
RXI/MOSI4: J19.3, U5.22
RXI/MOSI5: J23.3, U6.22
RXI/MOSI6: J27.3, U7.22
RXI/MOSI7: J31.3, U8.22
RXI/MOSI8: J35.3, U9.22
RXI/MOSI9: J39.3, U10.22
RXI/MOSI10: J43.3, U11.22
RXI/MOSI11: J47.3, U12.22
RXI/MOSI12: J51.3, U13.22
RXI/MOSI13: J55.3, U14.22
RXI/MOSI14: J59.3, U15.22
RXI/MOSI15: J63.3, U16.22
SCL/CLK: J1.4, J3.7, R4.1, U1.32
SCL/CLK1: J2.4, J7.7, R7.1, U2.32
SCL/CLK2: J9.4, J11.7, R12.1, U3.32
SCL/CLK3: J13.4, J15.7, R17.1, U4.32
SCL/CLK4: J17.4, J19.7, R22.1, U5.32
SCL/CLK5: J21.4, J23.7, R27.1, U6.32
SCL/CLK6: J25.4, J27.7, R32.1, U7.32
SCL/CLK7: J29.4, J31.7, R37.1, U8.32
SCL/CLK8: J33.4, J35.7, R42.1, U9.32
SCL/CLK9: J37.4, J39.7, R47.1, U10.32
SCL/CLK10: J41.4, J43.7, R52.1, U11.32
SCL/CLK11: J45.4, J47.7, R57.1, U12.32
SCL/CLK12: J49.4, J51.7, R62.1, U13.32
SCL/CLK13: J53.4, J55.7, R67.1, U14.32
SCL/CLK14: J57.4, J59.7, R72.1, U15.32
SCL/CLK15: J61.4, J63.7, R77.1, U16.32
SDA/CS: J1.3, J3.8, R3.1, U1.2
SDA/CS1: J2.3, J7.8, R6.1, U2.2
SDA/CS2: J9.3, J11.8, R11.1, U3.2
SDA/CS3: J13.3, J15.8, R16.1, U4.2
SDA/CS4: J17.3, J19.8, R21.1, U5.2
SDA/CS5: J21.3, J23.8, R26.1, U6.2
SDA/CS6: J25.3, J27.8, R31.1, U7.2
SDA/CS7: J29.3, J31.8, R36.1, U8.2
SDA/CS8: J33.3, J35.8, R41.1, U9.2
SDA/CS9: J37.3, J39.8, R46.1, U10.2
SDA/CS10: J41.3, J43.8, R51.1, U11.2
SDA/CS11: J45.3, J47.8, R56.1, U12.2
SDA/CS12: J49.3, J51.8, R61.1, U13.2
SDA/CS13: J53.3, J55.8, R66.1, U14.2
SDA/CS14: J57.3, J59.8, R71.1, U15.2
SDA/CS15: J61.3, J63.8, R76.1, U16.2
TIMEPULSE: J5.3, U1.33
TIMEPULSE1: J8.3, U2.33
TIMEPULSE2: J12.3, U3.33
TIMEPULSE3: J16.3, U4.33
TIMEPULSE4: J20.3, U5.33
TIMEPULSE5: J24.3, U6.33
TIMEPULSE6: J28.3, U7.33
TIMEPULSE7: J32.3, U8.33
TIMEPULSE8: J36.3, U9.33
TIMEPULSE9: J40.3, U10.33
TIMEPULSE10: J44.3, U11.33
TIMEPULSE11: J48.3, U12.33
TIMEPULSE12: J52.3, U13.33
TIMEPULSE13: J56.3, U14.33
TIMEPULSE14: J60.3, U15.33
TIMEPULSE15: J64.3, U16.33
TXO/MISO: J3.2, U1.21
TXO/MISO1: J7.2, U2.21
TXO/MISO2: J11.2, U3.21
TXO/MISO3: J15.2, U4.21
TXO/MISO4: J19.2, U5.21
TXO/MISO5: J23.2, U6.21
TXO/MISO6: J27.2, U7.21
TXO/MISO7: J31.2, U8.21
TXO/MISO8: J35.2, U9.21
TXO/MISO9: J39.2, U10.21
TXO/MISO10: J43.2, U11.21
TXO/MISO11: J47.2, U12.21
TXO/MISO12: J51.2, U13.21
TXO/MISO13: J55.2, U14.21
TXO/MISO14: J59.2, U15.21
TXO/MISO15: J63.2, U16.21
V_BATT: B1.+, R1.1, U1.16
V_BATT1: B2.+, R8.1, U2.16
V_BATT2: B3.+, R13.1, U3.16
V_BATT3: B4.+, R18.1, U4.16
V_BATT4: B5.+, R23.1, U5.16
V_BATT5: B6.+, R28.1, U6.16
V_BATT6: B7.+, R33.1, U7.16
V_BATT7: B8.+, R38.1, U8.16
V_BATT8: B9.+, R43.1, U9.16
V_BATT9: B10.+, R48.1, U10.16
V_BATT10: B11.+, R53.1, U11.16
V_BATT11: B12.+, R58.1, U12.16
V_BATT12: B13.+, R63.1, U13.16
V_BATT13: B14.+, R68.1, U14.16
V_BATT14: B15.+, R73.1, U15.16
V_BATT15: B16.+, R78.1, U16.16

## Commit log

2019-01-18 Initial Commit
    * Adds new Eagle Part for ZOE-M8
    * Has general design layout done unless a different battery option presents itself
    * Adds datasheet for part.
2019-01-22 Adds Buzzard Labels, finishes tracework (see description)
    * Moves diode and reistor
    * Fixes TSTOP on LGA
    * Moves uFL connector
    * Moves Jumpers
2019-01-23 Updates silk, adds new inductor, adds LED
2019-01-24 Adds pinout for FTDI connection, updates NDUC and ZOE footprints with tkeepout and tdocu, fixes silk labels
2019-01-25 Adds more silk labels, adds tkeepout around oscillator and more ground vias
2019-01-25 Removes one qwiic connector to make space for super capacitor, adds active antenna components (see description)
    * Adds 10 ohm resistor, ferrite bead, and 47pF capacitor.
2019-01-25 Adds more ground stitching vias
2019-01-26 Adds traces for unconnected ground pins, and changes 1k resistor to 100
2019-01-28 Moves left standoff to be symmetrical with right, and adds measurements to standoffs
2019-01-31 Adds new reflowable battery, updates battery, inductor, and IC with versions in the SparkFun Eagle Library
2019-01-31 Removes temporary library because all parts have been added to SparkFun Eagle Library
2019-02-04 Adds more ground vias, ZOE silk to topside, adjusts safteboot trace away from RF in, adds .1uF capactior
2019-02-05 Renames board files
2019-02-05 Updates schematic frame to letter size, updates parts (see description)
    * Battery part updated - replaces 100 Ohm series reistor with 3.3K
    * IC part updated - better pin names on symbol
    * Inductor part updated with better pads
    * 8 Pin connector added - moves SDA and SCL to their own through hole
    * Adds and fixes silk around design
    * Adds thermals to ground pour
2019-02-05 Moves Creative License text to the correct place.
2019-02-05 Adds VCC range and i2C Address to schematic.
2019-02-05 Adds production files and signature scorpion silk to underside of board.
2019-02-25 Removes some silk, changes version number, removes prototype gerber files
2019-02-26 Adds silk to battery terminals, adds initial mAH text to battery section in schematic.
2019-02-26 Adds no connect silk, fixes net labels that have active low pins
2019-02-26 Adds special ordering instructions and qwiic silk
2019-03-01 Updates Readme
2019-10-14 Adds production files, removes buzzard labels
2022-03-29 Removes note about battery capacity that is entirely made up (erroneously of course).
2022-04-07 Updates schematic

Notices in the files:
parts and their libraries:
SparkFun-Aesthetics: Licensing: Creative Commons ShareAlike 4.0 International - https://creativecommons.org/licenses/by-sa/4.0
SparkFun-Aesthetics: Released under the Creative Commons Attribution Share-Alike 4.0 License
SparkFun-Aesthetics: https://creativecommons.org/licenses/by-sa/4.0
